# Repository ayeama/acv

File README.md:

# Automotive CAN bus Visualiser (ACV)

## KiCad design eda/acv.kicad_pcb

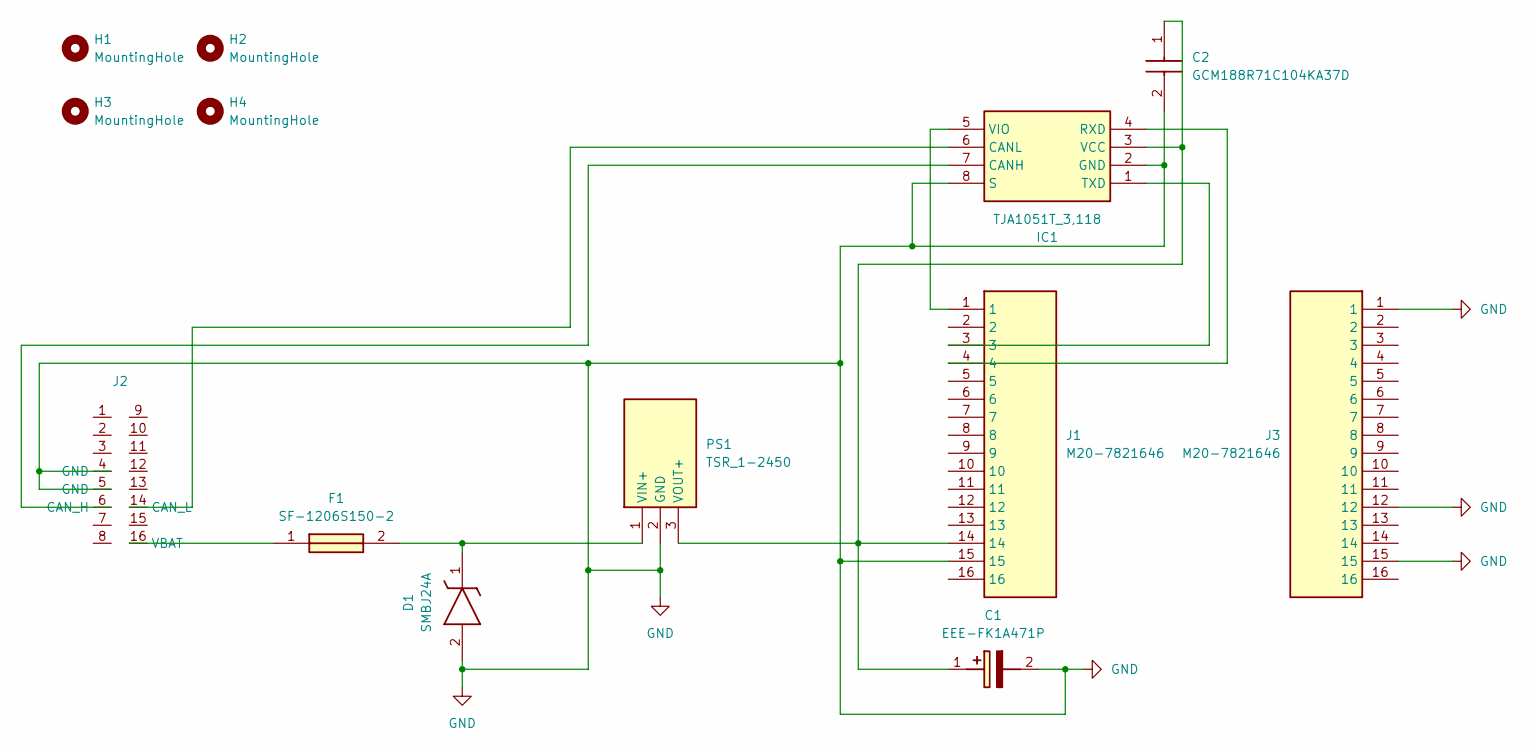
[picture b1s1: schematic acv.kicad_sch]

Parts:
C1: EEE-FK1A471P; EEHZT1E331UP; Mouser Part Number 667-EEE-FK1A471P
C2: GCM188R71C104KA37D; CAPC1608X90N; Mouser Part Number 81-GCM188R71C104KA7D
D1: SMBJ24A; DIOM5436X261N; Mouser Part Number 576-SMBJ24A
F1: SF-1206S150-2; FUSC3116X70N; Mouser Part Number 652-SF-1206S150-2
H1, H2, H3, H4: MountingHole; MountingHole_2.2mm_M2
IC1: TJA1051T_3,118; SOIC127P600X175-8N; Mouser Part Number 771-TJA1051T3118
J1, J3: M20-7821646; RHDR16W70P0X254_1X16_4104X250X850P; Mouser Part Number 855-M20-7821646
J2: OBD2_J1962_MALE_90
PS1: TSR_1-2450; TSR-1-24120; Mouser Part Number 495-TSR-1-2450

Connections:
GND: C1.2 (-), C2.2, D1.2 (A), IC1.2 (GND), IC1.8 (S), J1.15, J2.4 (GND), J2.5 (GND), J3.1, J3.12, J3.15, PS1.2 (GND)
unnamed: C1.1 (+), C2.1, IC1.3 (VCC), J1.14, PS1.3 (VOUT+)
unnamed: D1.1 (K), F1.2, PS1.1 (VIN+)
unnamed: IC1.7 (CANH), J2.6 (CAN_H)
unnamed: IC1.6 (CANL), J2.14 (CAN_L)
unnamed: IC1.4 (RXD), J1.4
unnamed: IC1.1 (TXD), J1.3
unnamed: IC1.5 (VIO), J1.1
unnamed: F1.1, J2.16 (VBAT)

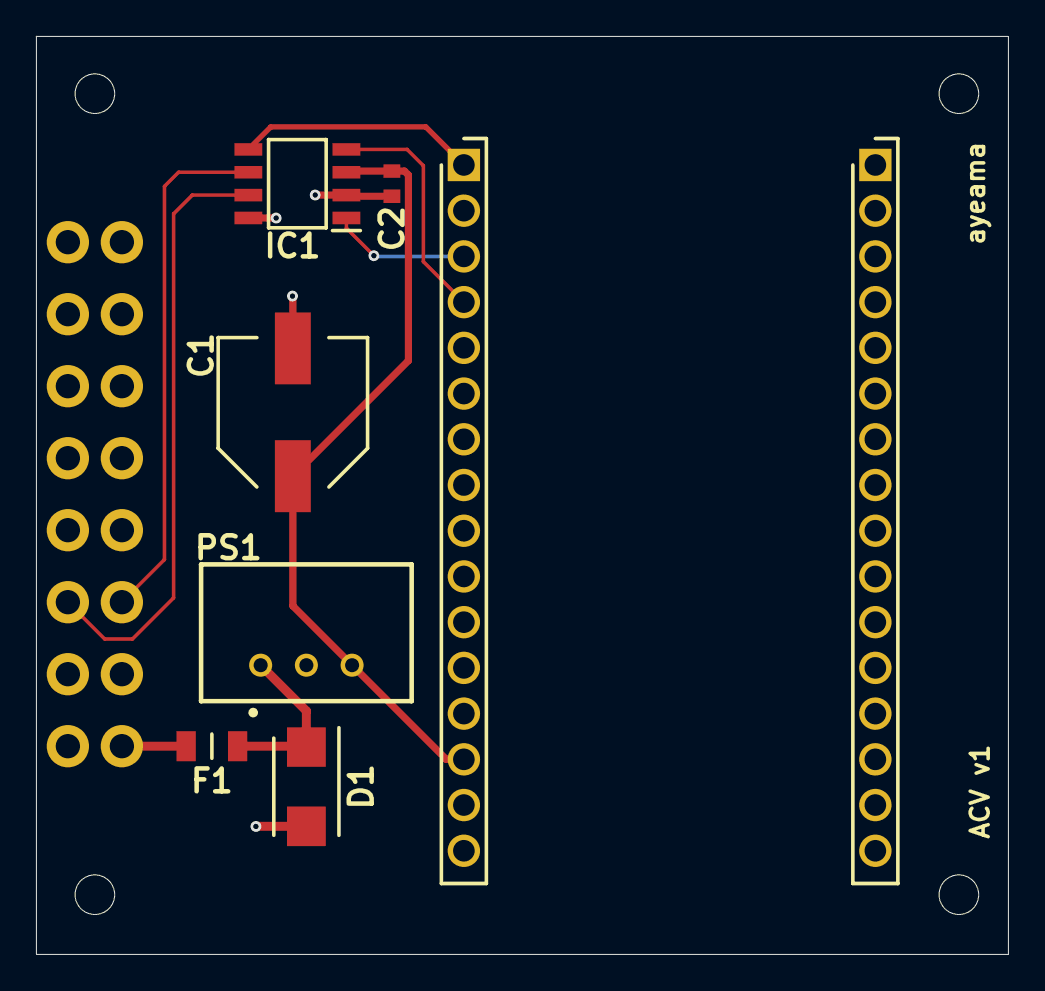
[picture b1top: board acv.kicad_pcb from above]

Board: 2 copper layers, 54.0 x 51.0 mm, 13 parts (0 on the bottom side), 9 nets.

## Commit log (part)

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2026-01-18 Add empty vue project
2026-01-18 Add empty esp-idf project
2026-01-18 Add empty kicad project
2026-01-21 Update frontend and backend
2026-01-30 Add OBD2 connector symbol and footprint
2026-01-31 Add CAN transceiver symbol and footprint
2026-02-11 Add led and twai backend tasks
2026-06-05 Remove old frontend
2026-06-05 Remove unused devcontainer
2026-06-05 Update backend
2026-06-05 Update EDA
2026-06-13 Update esp idf configuration
2026-06-13 CBR650R changes
2026-06-13 Config OBD2 function addressing and extended frame format
2026-06-14 Adding support for 11 and 29 bit identifiers
